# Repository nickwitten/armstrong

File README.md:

# ARMSTRONG

Armstrong is a functional electrical stimulation (FES) project aimed to help individuals with spinal chord injuries. The loss of dexterity in the fingers and hand makes day-to-day life much more difficult. The wearable watch has two electrodes that are placed on the user's arm to stimulate the forearm muscles which elicits a grasping motion.

The project contains two PCB designs located in
/ArmstrongPCB/
for a transformer based stimulation circuit and also a boost/H-bridge based stimulation circuit for more waveform options and amplitude.

The project also contains the firmware located in
/ArmstrongSoftware/
which can be flashed to an Arduino. There is separate firmware for the transformer based circuit and the boost/H-bridge based circuit.

The directory
/deliverables/
contains all of the design files that were used in the final product. A lot of other folders were used for exploring ideas and debugging.

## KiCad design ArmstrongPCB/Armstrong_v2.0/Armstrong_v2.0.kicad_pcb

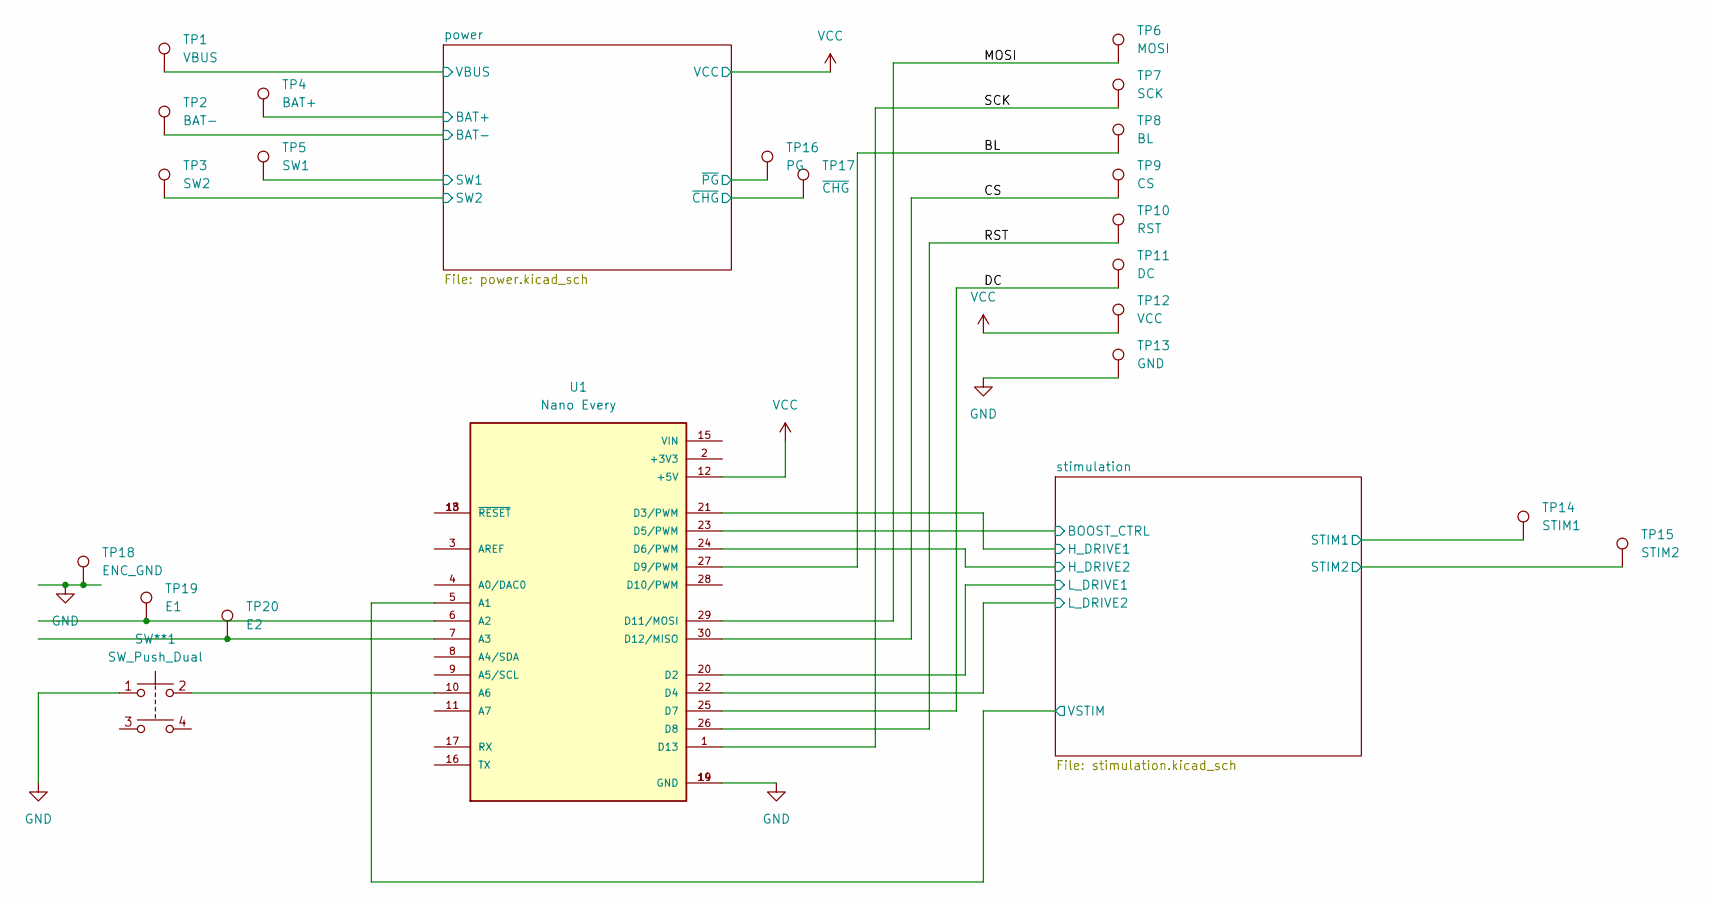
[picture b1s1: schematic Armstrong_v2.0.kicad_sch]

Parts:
SW**1: SW_Push_Dual; CS1204AF260-SMD
TP1: VBUS; TestPoint_THTPad_D2.0mm_Drill1.0mm
TP2: BAT-; TestPoint_THTPad_D2.0mm_Drill1.0mm
TP3: SW2; TestPoint_THTPad_D2.0mm_Drill1.0mm
TP4: BAT+; TestPoint_THTPad_D2.0mm_Drill1.0mm
TP5: SW1; TestPoint_THTPad_D2.0mm_Drill1.0mm
TP6: MOSI; TestPoint_Pad_D1.5mm
TP7: SCK; TestPoint_Pad_D1.5mm
TP8: BL; TestPoint_Pad_D1.5mm
TP9: CS; TestPoint_Pad_D1.5mm
TP10: RST; TestPoint_Pad_D1.5mm
TP11: DC; TestPoint_Pad_D1.5mm
TP12: VCC; TestPoint_Pad_D1.5mm
TP13: GND; TestPoint_Pad_D1.5mm
TP14: STIM1; TestPoint_THTPad_D2.0mm_Drill1.0mm
TP15: STIM2; TestPoint_THTPad_D2.0mm_Drill1.0mm
TP16: PG; TestPoint_Pad_D1.0mm
TP17: ~{CHG}; TestPoint_Pad_D1.0mm
TP18: ENC_GND; TestPoint_THTPad_D2.0mm_Drill1.0mm
TP19: E1; TestPoint_THTPad_D2.0mm_Drill1.0mm
TP20: E2; TestPoint_THTPad_D2.0mm_Drill1.0mm
U1: Nano Every; PARTREV 6-11-19

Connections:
/BL: TP8.1, U1.27 (D9/PWM)
/CS: TP9.1, U1.30 (D12/MISO)
/DC: TP11.1, U1.25 (D7)
/MOSI: TP6.1, U1.29 (D11/MOSI)
/RST: TP10.1, U1.26 (D8)
/SCK: TP7.1, U1.1 (D13)
/power/BAT+: TP4.1, TP5.1; also elsewhere on the board
/power/VBUS: TP1.1; also elsewhere on the board
/power/~CHG: TP17.1; also elsewhere on the board
/power/~PG: TP16.1; also elsewhere on the board
/stimulation/BOOST_CTRL: U1.23 (D5/PWM); also elsewhere on the board
/stimulation/H_DRIVE1: U1.21 (D3/PWM); also elsewhere on the board
/stimulation/H_DRIVE2: U1.24 (D6/PWM); also elsewhere on the board
/stimulation/L_DRIVE1: U1.20 (D2); also elsewhere on the board
/stimulation/L_DRIVE2: U1.22 (D4); also elsewhere on the board
/stimulation/STIM1: TP14.1; also elsewhere on the board
/stimulation/STIM2: TP15.1; also elsewhere on the board
/stimulation/VSTIM: U1.5 (A1); also elsewhere on the board
GND: SW**1.1, TP2.1, TP13.1, TP18.1, U1.14 (GND), U1.19 (GND); also elsewhere on the board
unnamed: TP19.1, U1.6 (A2)
unnamed: TP20.1, U1.7 (A3)
unnamed: SW**1.2, U1.10 (A6)
unnamed: U1.13 (~RESET), U1.18 (~RESET)
VCC: TP3.1, TP12.1, U1.12 (+5V); also elsewhere on the board

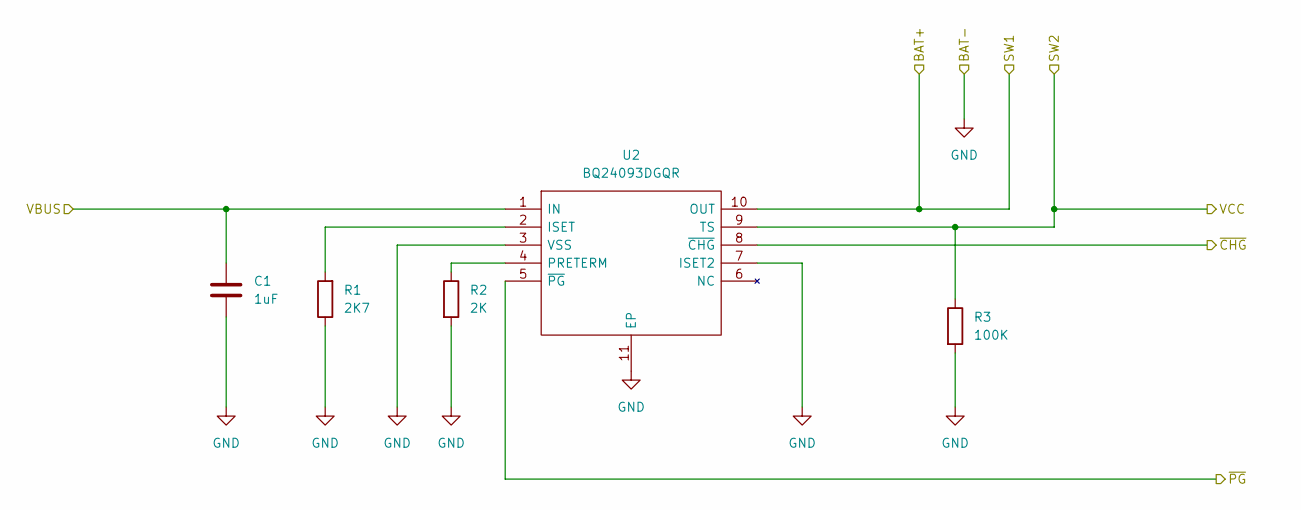
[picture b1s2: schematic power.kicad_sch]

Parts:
C1: 1uF; C_1206_3216Metric_Pad1.33x1.80mm_HandSolder
R1: 2K7; R_1206_3216Metric_Pad1.30x1.75mm_HandSolder
R2: 2K; R_1206_3216Metric_Pad1.30x1.75mm_HandSolder
R3: 100K; R_1206_3216Metric_Pad1.30x1.75mm_HandSolder
U2: BQ24093DGQR; Mouser Part Number 595-BQ24093DGQR

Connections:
/power/BAT+: U2.10 (OUT); also elsewhere on the board
/power/VBUS: C1.1, U2.1 (IN); also elsewhere on the board
/power/~CHG: U2.8 (~CHG); also elsewhere on the board
/power/~PG: U2.5 (~PG); also elsewhere on the board
GND: C1.2, R1.1, R2.2, R3.2, U2.3 (VSS), U2.7 (ISET2), U2.11 (EP); also elsewhere on the board
unnamed: R1.2, U2.2 (ISET)
unnamed: R2.1, U2.4 (PRETERM)
VCC: R3.1, U2.9 (TS); also elsewhere on the board

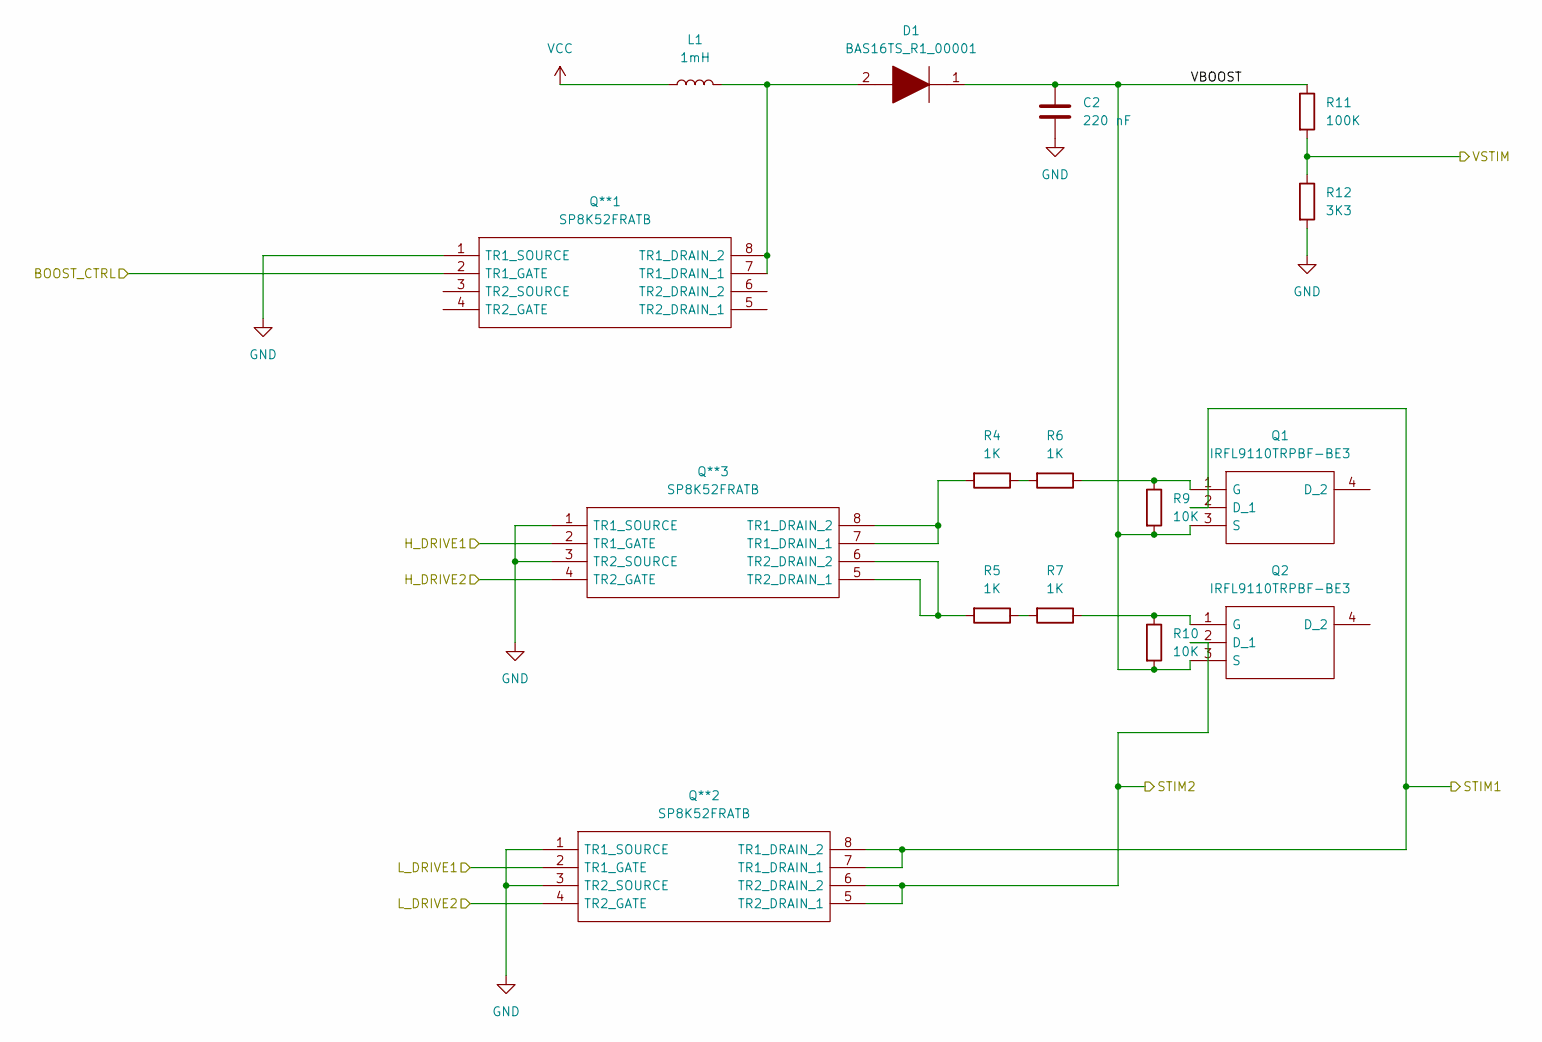
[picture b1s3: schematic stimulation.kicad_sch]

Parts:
C2: 220 nF; C_1206_3216Metric_Pad1.33x1.80mm_HandSolder
D1: BAS16TS_R1_00001; Manufacturer_Part_Number BAS16TS_R1_00001; Mouser Part Number 241-BAS16TS_R1_00001
L1: 1mH; LPS6225-105MRC
Q1, Q2: IRFL9110TRPBF-BE3; Mouser Part Number 78-IRFL9110TRPBF-BE3
Q**1, Q**2, Q**3: SP8K52FRATB; Manufacturer_Part_Number SP8K52FRATB; Mouser Part Number 755-SP8K52FRATB
R4, R5, R6, R7: 1K; R_1206_3216Metric_Pad1.30x1.75mm_HandSolder
R9, R10: 10K; R_1206_3216Metric_Pad1.30x1.75mm_HandSolder
R11: 100K; R_1206_3216Metric_Pad1.30x1.75mm_HandSolder
R12: 3K3; R_1206_3216Metric_Pad1.30x1.75mm_HandSolder

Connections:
/stimulation/BOOST_CTRL: Q**1.2 (TR1_GATE); also elsewhere on the board
/stimulation/H_DRIVE1: Q**3.2 (TR1_GATE); also elsewhere on the board
/stimulation/H_DRIVE2: Q**3.4 (TR2_GATE); also elsewhere on the board
/stimulation/L_DRIVE1: Q**2.2 (TR1_GATE); also elsewhere on the board
/stimulation/L_DRIVE2: Q**2.4 (TR2_GATE); also elsewhere on the board
/stimulation/STIM1: Q1.2 (D_1), Q**2.7 (TR1_DRAIN_1), Q**2.8 (TR1_DRAIN_2); also elsewhere on the board
/stimulation/STIM2: Q2.2 (D_1), Q**2.5 (TR2_DRAIN_1), Q**2.6 (TR2_DRAIN_2); also elsewhere on the board
/stimulation/VBOOST: C2.1, D1.1, Q1.3 (S), Q2.3 (S), R9.2, R10.2, R11.1
/stimulation/VSTIM: R11.2, R12.1; also elsewhere on the board
GND: C2.2, Q**1.1 (TR1_SOURCE), Q**2.1 (TR1_SOURCE), Q**2.3 (TR2_SOURCE), Q**3.1 (TR1_SOURCE), Q**3.3 (TR2_SOURCE), R12.2; also elsewhere on the board
unnamed: D1.2, L1.2, Q**1.7 (TR1_DRAIN_1), Q**1.8 (TR1_DRAIN_2)
unnamed: Q1.1 (G), R6.1, R9.1
unnamed: Q2.1 (G), R7.1, R10.1
unnamed: Q**3.5 (TR2_DRAIN_1), Q**3.6 (TR2_DRAIN_2), R5.2
unnamed: Q**3.7 (TR1_DRAIN_1), Q**3.8 (TR1_DRAIN_2), R4.2
unnamed: R4.1, R6.2
unnamed: R5.1, R7.2
VCC: L1.1; also elsewhere on the board

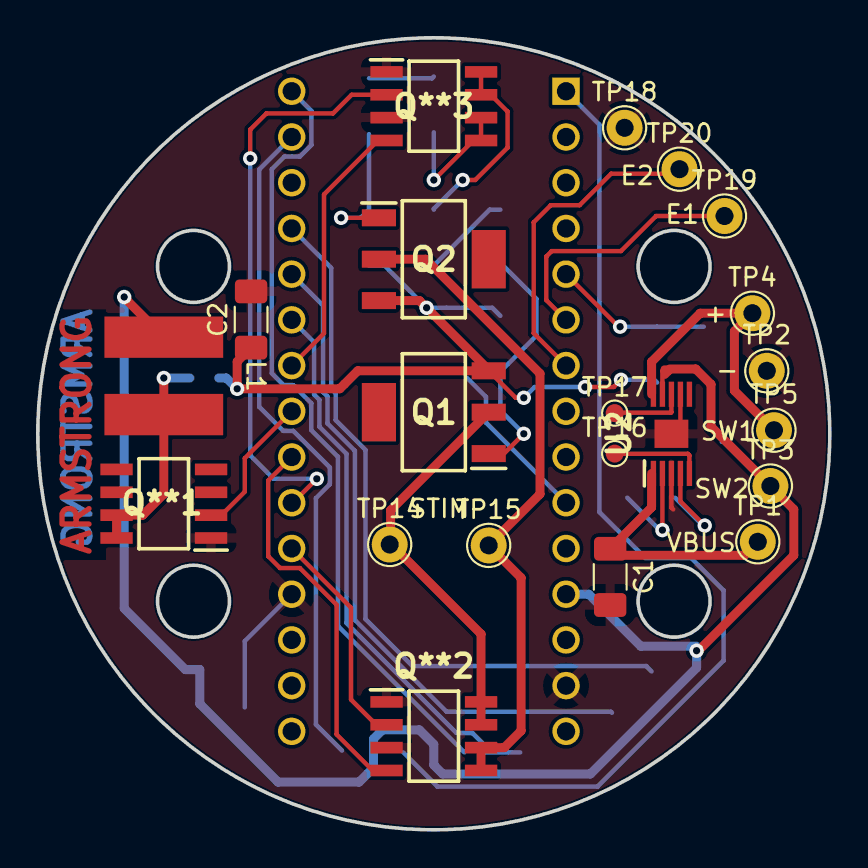
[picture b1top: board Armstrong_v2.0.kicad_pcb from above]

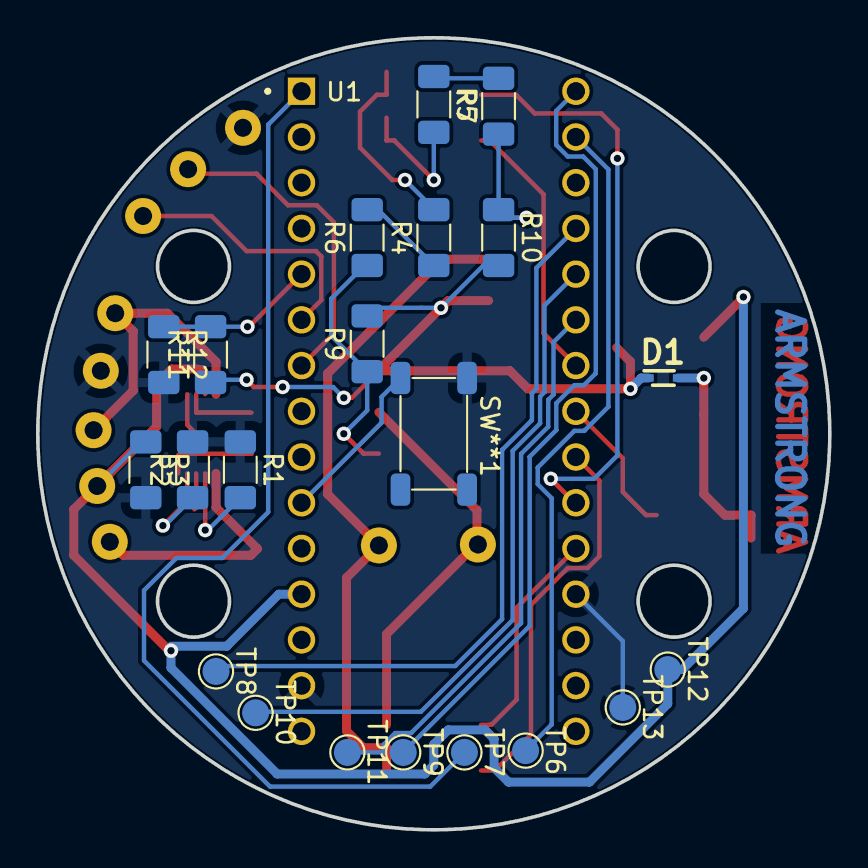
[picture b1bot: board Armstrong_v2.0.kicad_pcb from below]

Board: 2 copper layers, 44.0 x 44.0 mm, 43 parts (22 on the bottom side), 34 nets.

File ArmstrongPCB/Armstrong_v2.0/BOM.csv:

"Id";"Designator";"Package";"Quantity";"Designation";"Supplier and ref";
1;"SW**1";"CS1204AF260-SMD";1;"SW_Push_Dual";;;
2;"TP17";"TestPoint_Pad_D1.0mm";1;"~{CHG}";;;
3;"TP16";"TestPoint_Pad_D1.0mm";1;"PG";;;
4;"C2";"C_1206_3216Metric_Pad1.33x1.80mm_HandSolder";1;"220 nF";;;
5;"C1";"C_1206_3216Metric_Pad1.33x1.80mm_HandSolder";1;"1uF";;;
6;"D1";"BAS16TS_R1_00001";1;"BAS16TS_R1_00001";;;
7;"R12";"R_1206_3216Metric_Pad1.30x1.75mm_HandSolder";1;"3K3";;;
8;"R11,R3";"R_1206_3216Metric_Pad1.30x1.75mm_HandSolder";2;"100K";;;
9;"R10,R9";"R_1206_3216Metric_Pad1.30x1.75mm_HandSolder";2;"10K";;;
10;"R7,R6,R5,R4";"R_1206_3216Metric_Pad1.30x1.75mm_HandSolder";4;"1K";;;
11;"R2";"R_1206_3216Metric_Pad1.30x1.75mm_HandSolder";1;"2K";;;
12;"R1";"R_1206_3216Metric_Pad1.30x1.75mm_HandSolder";1;"2K7";;;
13;"TP13";"TestPoint_Pad_D1.5mm";1;"GND";;;
14;"TP12";"TestPoint_Pad_D1.5mm";1;"VCC";;;
15;"TP11";"TestPoint_Pad_D1.5mm";1;"DC";;;
16;"TP10";"TestPoint_Pad_D1.5mm";1;"RST";;;
17;"TP9";"TestPoint_Pad_D1.5mm";1;"CS";;;
18;"TP8";"TestPoint_Pad_D1.5mm";1;"BL";;;
19;"TP7";"TestPoint_Pad_D1.5mm";1;"SCK";;;
20;"TP6";"TestPoint_Pad_D1.5mm";1;"MOSI";;;
21;"TP4";"TestPoint_THTPad_D2.0mm_Drill1.0mm";1;"BAT+";;;
22;"TP3";"TestPoint_THTPad_D2.0mm_Drill1.0mm";1;"SW2";;;
23;"Q**2,Q**3,Q**1";"SP8K52FRATB";3;"SP8K52FRATB";;;
24;"TP15";"TestPoint_THTPad_D2.0mm_Drill1.0mm";1;"STIM2";;;
25;"U1";"Nano Every";1;"Nano Every";;;
26;"L1";"LPS6225-105MRC";1;"1mH";;;
27;"TP14";"TestPoint_THTPad_D2.0mm_Drill1.0mm";1;"STIM1";;;
28;"TP2";"TestPoint_THTPad_D2.0mm_Drill1.0mm";1;"BAT-";;;
29;"TP5";"TestPoint_THTPad_D2.0mm_Drill1.0mm";1;"SW1";;;
30;"Q2,Q1";"IRFL9110TRPBF-BE3";2;"IRFL9110TRPBF-BE3";;;
31;"U2";"BQ24093DGQR";1;"BQ24093DGQR";;;
32;"TP1";"TestPoint_THTPad_D2.0mm_Drill1.0mm";1;"VBUS";;;

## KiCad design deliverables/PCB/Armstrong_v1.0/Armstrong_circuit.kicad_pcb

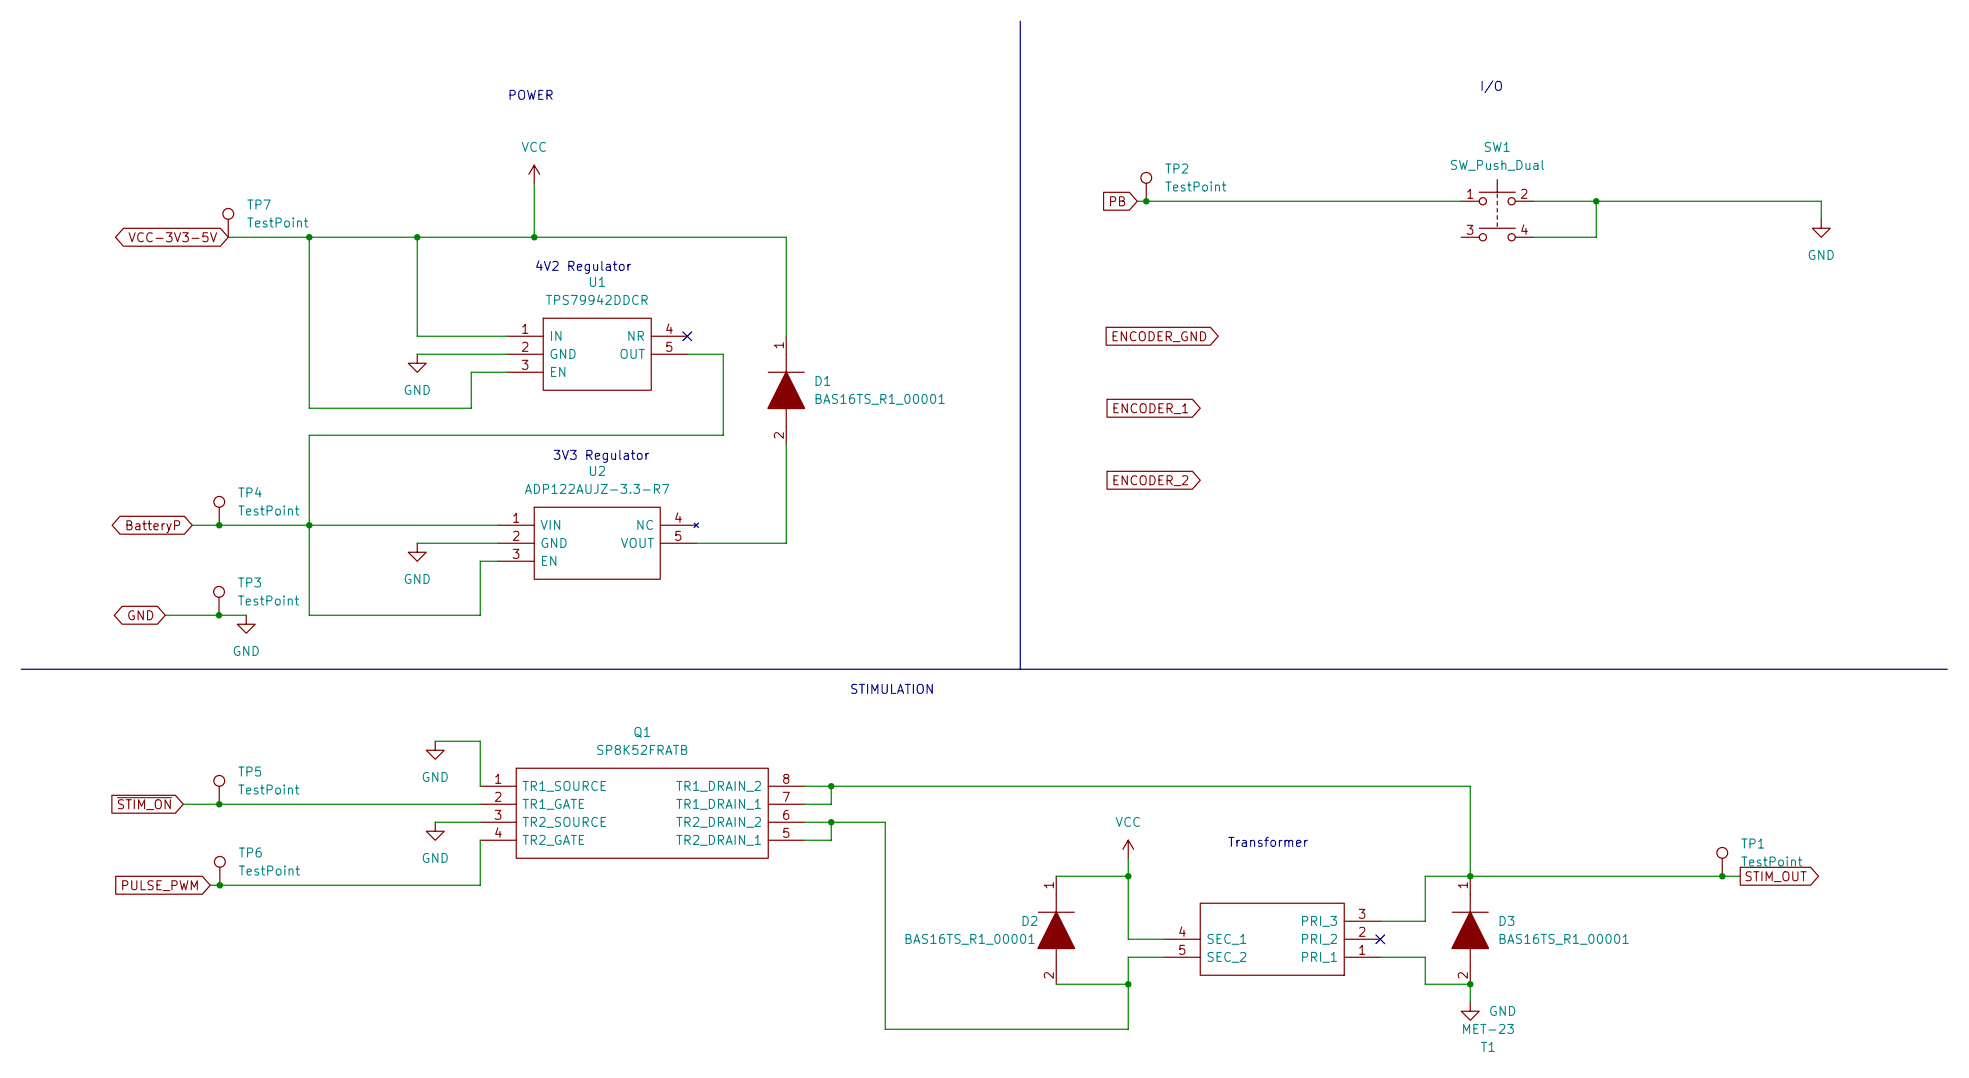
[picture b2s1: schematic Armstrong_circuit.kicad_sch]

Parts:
D1, D2, D3: BAS16TS_R1_00001; Manufacturer_Part_Number BAS16TS_R1_00001; Mouser Part Number 241-BAS16TS_R1_00001
Q1: SP8K52FRATB; Manufacturer_Part_Number SP8K52FRATB; Mouser Part Number 755-SP8K52FRATB
SW1: SW_Push_Dual; CS1204AF260-SMD
T1: MET-23; MET-23-SIDE; Manufacturer_Part_Number MET-23; Mouser Part Number 838-MET-23
TP1, TP2, TP3, TP4, TP5, TP6, TP7: TestPoint; TestPoint_Pad_1.0x1.0mm
U1: TPS79942DDCR; ADP162AUJZ-4.2-R7; Manufacturer_Part_Number TPS79942DDCR; Mouser Part Number 595-TPS79942DDCR
U2: ADP122AUJZ-3.3-R7; Manufacturer_Part_Number ADP122AUJZ-3.3-R7; Mouser Part Number 584-ADP122AUJZ-3.3R7

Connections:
BatteryP: TP4.1, U1.5 (OUT), U2.1 (VIN), U2.3 (EN)
GND: D3.2, Q1.1 (TR1_SOURCE), Q1.3 (TR2_SOURCE), SW1.2, SW1.4, T1.1 (PRI_1), TP3.1, U1.2 (GND), U2.2 (GND)
unnamed: D1.2, U2.5 (VOUT)
unnamed: D2.2, Q1.5 (TR2_DRAIN_1), Q1.6 (TR2_DRAIN_2), T1.5 (SEC_2)
PB: SW1.1, TP2.1
PULSE_PWM: Q1.4 (TR2_GATE), TP6.1
STIM_OUT: D3.1, Q1.7 (TR1_DRAIN_1), Q1.8 (TR1_DRAIN_2), T1.3 (PRI_3), TP1.1
VCC-3V3-5V: D1.1, D2.1, T1.4 (SEC_1), TP7.1, U1.1 (IN), U1.3 (EN)
~STIM_ON: Q1.2 (TR1_GATE), TP5.1

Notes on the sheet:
STIMULATION
I/O
3V3 Regulator
4V2 Regulator
POWER
Transformer

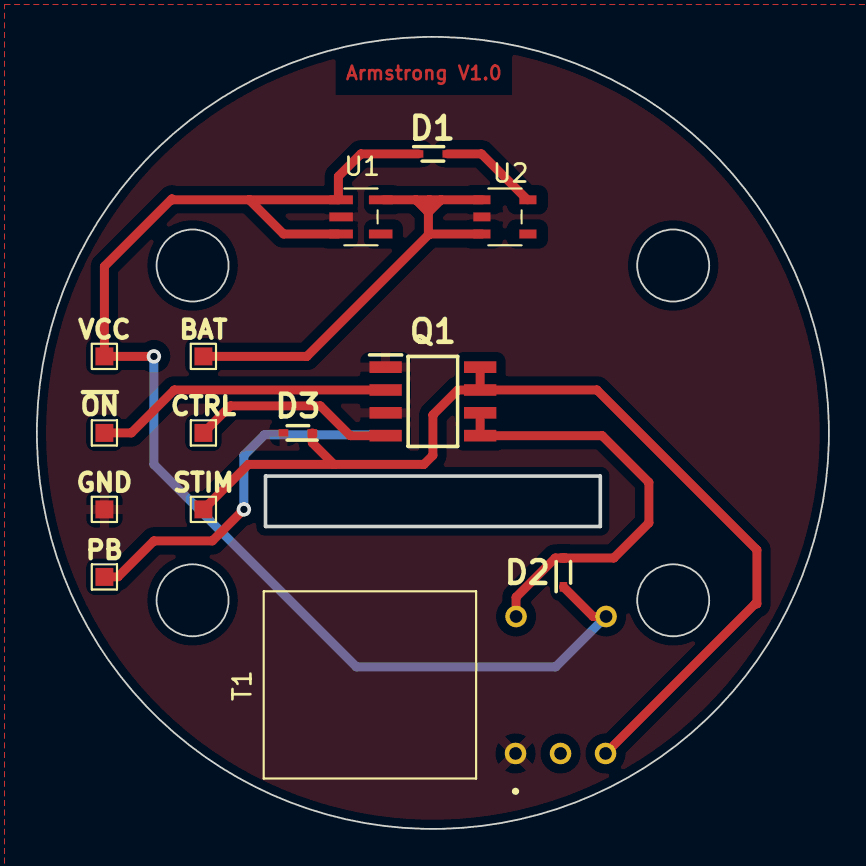
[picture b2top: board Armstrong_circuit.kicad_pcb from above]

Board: 2 copper layers, 43.9 x 43.9 mm, 15 parts (1 on the bottom side), 9 nets.

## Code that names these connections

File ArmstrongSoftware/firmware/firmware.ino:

#include "firmware.h"


const uint32_t boost_period_ticks = TCA_FREQ / BOOST_FREQ;
const uint8_t pulse_delay_ticks = 1;

volatile uint32_t ovf_count = 0;
volatile uint8_t dir = 0;

volatile uint32_t pulse_period_ovf;
volatile uint32_t pulse_duty_ovf;
volatile float boost_duty;
volatile uint8_t waveform_type;

void waveform_param_set(uint32_t frequency, float duty, float amplitude, enum waveform type) {
    if (type == OFF) {
        TCA0.SINGLE.CTRLA &= ~TCA_SINGLE_ENABLE_bm;
    } else {
        TCA0.SINGLE.CTRLA |= TCA_SINGLE_ENABLE_bm;
    }
    pulse_period_ovf = BOOST_FREQ / frequency;  // Amount of TCA0 overflows for pulse period
    pulse_duty_ovf = BOOST_FREQ / frequency * duty;  // Amount of TCA0 overflows for pulse duty
    boost_duty = amplitude;
    waveform_type = type;
}

unsigned long scaled_millis(void) {
    return millis() / 16;  // TCA is running 16 times the normal speed
}

void scaled_delay(unsigned long ms) {
    delay(ms * 16);  // TCA is running 16 times the normal speed
}

/* Turn on the high side to either output line
   direction:
        0 - line 1
        >= 1 - line 2
*/
static inline void set_pulse_line_on(uint8_t direction) {
    if (direction) {
        PORTF.OUTCLR = PIN5_bm;  // Turn off H_DRIVE1
        PORTC.OUTCLR = PIN6_bm;  // Turn off L_DRIVE2
        PORTA.OUTSET = PIN0_bm;  // Turn on L_DRIVE1
        PORTF.OUTSET = PIN4_bm;  // Turn on H_DRIVE2
    } else {
        PORTF.OUTCLR = PIN4_bm;  // Turn off H_DRIVE2
        PORTA.OUTCLR = PIN0_bm;  // Turn off L_DRIVE1
        PORTC.OUTSET = PIN6_bm;  // Turn on L_DRIVE2
        PORTF.OUTSET = PIN5_bm;  // Turn on H_DRIVE1
    }
}

static inline void set_pulse_line_off(void) {
    PORTF.OUTCLR = PIN5_bm;  // Turn off H_DRIVE1
    PORTF.OUTCLR = PIN4_bm;  // Turn off H_DRIVE2
}

void pulse_init(void) {
    // Digital writes
    PORTF.DIRSET = PIN5_bm;  // H_DRIVE1
    PORTF.DIRSET = PIN4_bm;  // H_DRIVE2
    PORTA.DIRSET = PIN0_bm;  // L_DRIVE1
    PORTC.DIRSET = PIN6_bm;  // L_DRIVE2

    // PWM TCA Output Channel
    PORTB.DIRSET = PIN2_bm;  // D5, PB2 TCA_CMP2

    // Timer A Setup
    #ifdef TCA_FREQ
    TCA0.SINGLE.CTRLA = TCA_SINGLE_CLKSEL_DIV4_gc;  // Set clock, TCA_FREQ should correspond to this div value
    #endif
    TCA0.SINGLE.CTRLB = TCA_SINGLE_CMP2EN_bm | TCA_SINGLE_WGMODE_SINGLESLOPE_gc;  // Single slope and enable channel 2
    TCA0.SINGLE.PERBUF = boost_period_ticks;  // Set the period
    TCA0.SINGLE.CMP2BUF = 0;  // Set the duty-cycle
    TCA0.SINGLE.INTCTRL = TCA_SINGLE_CMP2_bm | TCA_SINGLE_OVF_bm;  // Setup interrupts to fire on cmp2  

    // Initialize timing parameters
    waveform_param_set(100, 0, 0, OFF);

    // Enable timer
    TCA0.SINGLE.CTRLA |= TCA_SINGLE_ENABLE_bm;
}

ISR(TCA0_CMP2_vect) {
    TCA0.SINGLE.INTFLAGS |= TCA_SINGLE_CMP2_bm;
}

ISR(TCA0_OVF_vect) {
    if (ovf_count < pulse_duty_ovf + pulse_delay_ticks) {
        TCA0.SINGLE.CMP2BUF = boost_period_ticks * boost_duty;  // Set the duty-cycle
        if (ovf_count >= pulse_delay_ticks) {
            set_pulse_line_on(dir);
        }
    } else {
        set_pulse_line_off();
        // TCA0.SINGLE.CMP2BUF = 0;
    }

    if (ovf_count >= pulse_period_ovf - 1) {  // End of pulse period
        if (waveform_type == DIFFERENTIAL | waveform_type == ASCENDING_DIFFERENTIAL) {
            dir = ~dir;
        }
        ovf_count = 0;
    } else {
        ovf_count++;
    }

    TCA0.SINGLE.INTFLAGS |= TCA_SINGLE_OVF_bm;  // Clear interrupt flag
}

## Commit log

2022-11-25 Init master senior design repo
2022-11-25 Rename software repo
2022-11-28 V2 firmware start, V2 pinout, Timer setup
2022-11-28 v2_firmware waveforms and driver functions
2022-11-28 update ArmstrongSoftware
2022-12-14 add deliverables folder
2022-12-14 Add mechanical to deliverables
2022-12-14 rename app_v1 in deliverables
2022-12-14 Add BOM to delivarables
2022-12-22 last bit of files
2022-12-22 Update software submodule
2022-12-22 Move submodules into this repo
2022-12-22 readme.md
2022-12-22 readme update

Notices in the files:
parts and their libraries:
Copyright 2021 Accelerated Designs. All rights reserved.
